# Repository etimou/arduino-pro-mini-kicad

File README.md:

# arduino-pro-mini-kicad
This is a clone of the well known arduino board "pro-mini" designed in kicad while the original was designed in eagle. Ref https://store.arduino.cc/arduino-pro-mini

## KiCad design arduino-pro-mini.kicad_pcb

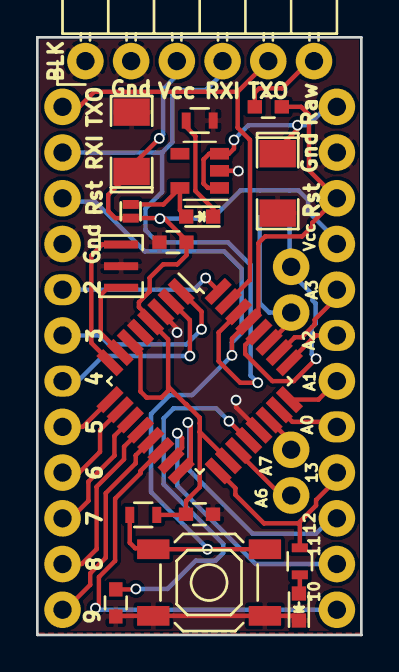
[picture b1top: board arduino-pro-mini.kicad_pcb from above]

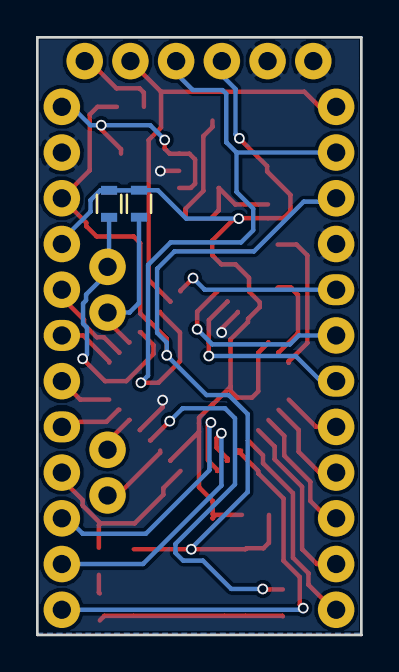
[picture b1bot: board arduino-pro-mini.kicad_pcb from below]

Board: 2 copper layers, 18.0 x 33.2 mm, 23 parts (2 on the bottom side), 33 nets.

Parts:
C1, C2, C3, C10: 0.1uF; C_0603
C13, C19: 10uF; SMD-1206_Pol
D3: Green; LED_0603
JP1: CONN_01X06; Pin_Header_Angled_1x06
JP2, JP3: CONN_01X02; Pin_Header_Straight_1x02
JP6, JP7: CONN_01X12; Pin_Header_Straight_1x12
LED1: Red; LED_0603
Q1: Resonator; Resonator_smd
R1, R3: R; R_0603
R2, R11: 10k; R_0603
R6: 330; R_0603
S1: Reset; SW_SPST_SKQG
SJ1: Jumper_NO_Small; jumper
U1: ATMEGA328-A; TQFP-32_7x7mm_Pitch0.8mm
U2: MIC5205; SOT-23-5

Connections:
A0: JP6.8, U1.23
A1: JP6.7, U1.24
A2: JP6.6, U1.25
A3: JP6.5, U1.26
A4: JP2.1, R1.2, U1.27
A5: JP2.2, R3.2, U1.28
A6: JP3.1, U1.19
A7: JP3.2, U1.22
D2: JP7.8, U1.32
D3: JP7.7, U1.1
D4: JP7.6, U1.2
D5: JP7.5, U1.9
D6: JP7.4, U1.10
D7: JP7.3, U1.11
D8: JP7.2, U1.12
D9: JP7.1, U1.13
D10: JP6.12, U1.14
DTR: C2.1, JP1.6
GND: C1.2, C3.2, C10.2, C13.2, C19.2, D3.1, JP1.1, JP1.2, JP6.2, JP7.9, Q1.2, R11.2, S1.1, U1.3, U1.5, U1.21, U2.2
MISO: JP6.10, U1.16
MOSI: JP6.11, U1.15
unnamed: C1.1, U1.20
unnamed: D3.2, R6.1
unnamed: LED1.1, R11.1
unnamed: LED1.2, SJ1.1, U2.5
unnamed: Q1.1, U1.8
unnamed: Q1.3, U1.7
RAW: C19.1, JP6.1, U2.1, U2.3
RESET: C2.2, JP6.3, JP7.10, R2.2, S1.2, U1.29
RXI: JP1.4, JP7.11, U1.30
SCK: JP6.9, R6.2, U1.17
TXO: JP1.5, JP7.12, U1.31
VCC: C3.1, C10.1, C13.1, JP1.3, JP6.4, R1.1, R2.1, R3.1, SJ1.2, U1.4, U1.6, U1.18

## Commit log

2017-12-25 add design files
2017-12-25 add pictures
2017-12-27 update pictures
2017-12-28 added pin labels
